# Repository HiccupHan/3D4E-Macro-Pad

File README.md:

# 3D4E Macro Pad
 3 * 3 macropad with OLED screen and rotary encoder

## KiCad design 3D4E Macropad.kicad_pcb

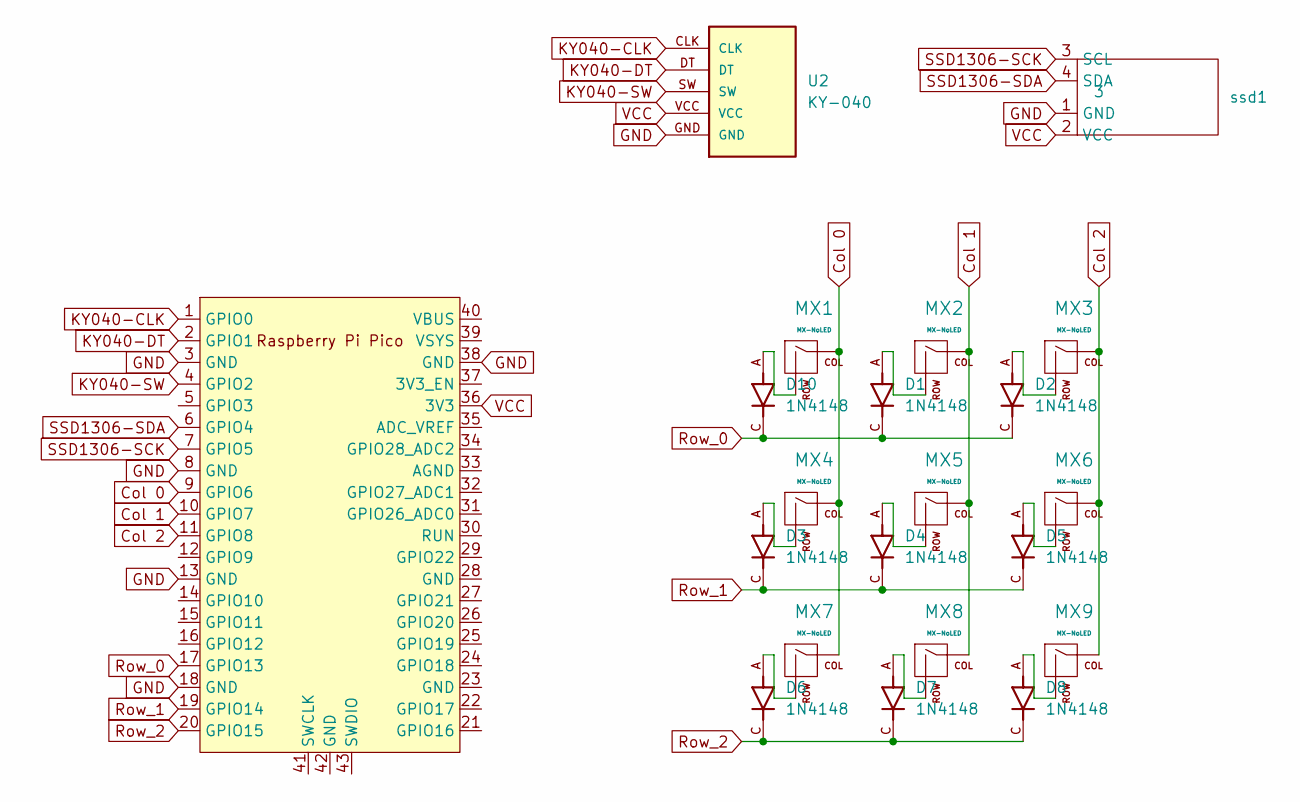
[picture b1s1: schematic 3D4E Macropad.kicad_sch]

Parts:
D1, D2, D3, D4, D5, D6, D7, D8, D10: 1N4148; DIOAD829W49L456D191
MX1, MX2, MX3, MX4, MX5, MX6, MX7, MX8, MX9: MX-NoLED; MX-1U-NoLED
U1: Pico; RPi_Pico_SMD_TH
U2: KY-040; KY-040-PORT
ssd1: 3; SSD1306-0.91-OLED-4pin-128x32

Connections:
Col 0: MX1.1 (COL), MX4.1 (COL), MX7.1 (COL), U1.9 (GPIO6)
Col 1: MX2.1 (COL), MX5.1 (COL), MX8.1 (COL), U1.10 (GPIO7)
Col 2: MX3.1 (COL), MX6.1 (COL), MX9.1 (COL), U1.11 (GPIO8)
GND: U1.3 (GND), U1.8 (GND), U1.13 (GND), U1.18 (GND), U1.38 (GND), U2.GND, ssd1.1 (GND)
KY040-CLK: U1.1 (GPIO0), U2.CLK
KY040-DT: U1.2 (GPIO1), U2.DT
KY040-SW: U1.4 (GPIO2), U2.SW
unnamed 7: D10.A, MX1.2 (ROW); also elsewhere on the board
unnamed: D1.A, MX2.2 (ROW)
unnamed: D2.A, MX3.2 (ROW)
unnamed: D3.A, MX4.2 (ROW)
unnamed: D4.A, MX5.2 (ROW)
unnamed: D5.A, MX6.2 (ROW)
unnamed: D6.A, MX7.2 (ROW)
unnamed: D7.A, MX8.2 (ROW)
unnamed: D8.A, MX9.2 (ROW)
Row_0: D1.C, D2.C, D10.C, U1.17 (GPIO13); also elsewhere on the board
Row_1: D3.C, D4.C, D5.C, U1.19 (GPIO14)
Row_2: D6.C, D7.C, D8.C, U1.20 (GPIO15)
SSD1306-SCK: U1.7 (GPIO5), ssd1.3 (SCL)
SSD1306-SDA: U1.6 (GPIO4), ssd1.4 (SDA)
VCC: U1.36 (3V3), U2.VCC, ssd1.2 (VCC)

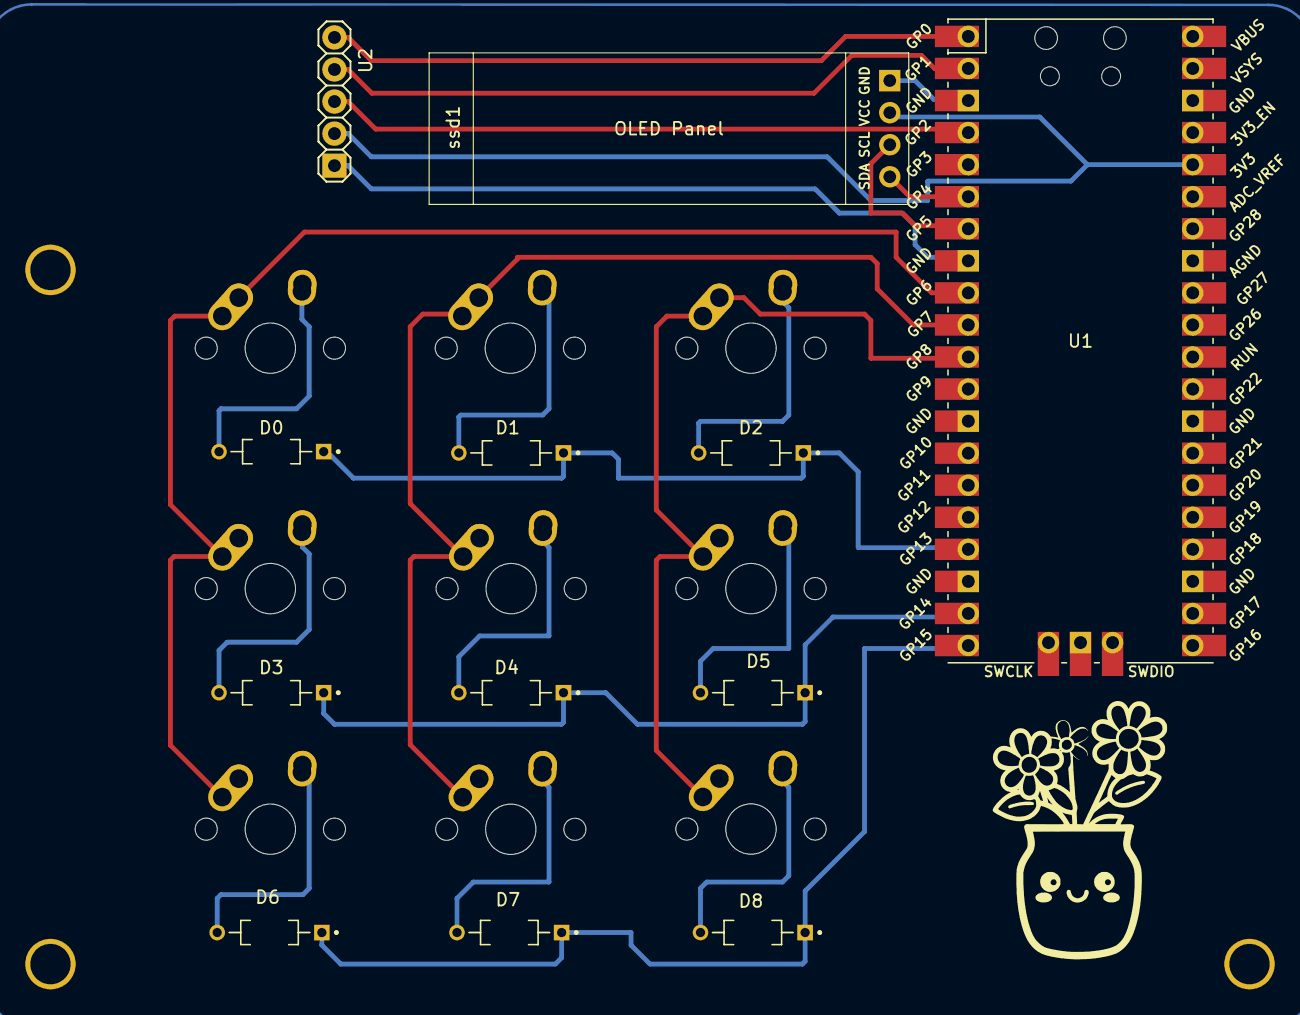
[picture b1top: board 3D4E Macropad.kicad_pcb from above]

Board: 2 copper layers, 24 parts (0 on the bottom side), 22 nets.

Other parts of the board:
D0: 1N4148; DIOAD829W49L456D191
HOLE_M3, HOLE_M3#2, HOLE_M3#3: VAL**; HOLE_M3

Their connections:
unnamed 7: D0.A; also elsewhere on the board
Row_0: D0.C; also elsewhere on the board

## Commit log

2023-10-26 new macro pad
2023-11-03 macropad update final
2024-04-18 Minor fixes
    - need to fix orientation of the rotary encoder
2024-05-09 fixed positioning of rotary encoder pcb
2024-05-09 bongo cat svg
2024-05-09 flowerpot svg
2024-07-21 update to graphics
